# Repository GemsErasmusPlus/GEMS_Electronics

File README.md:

# GEMS_Electronics
GEMS_Electronics repository contains selected results of Erasmus+ project GEMS that are directly related to the electronics design for the GEMS educational hardware.

Project [**GEMS**](https://gems-erasmus.eu/) - Graceful Equalising of Mechatronics Students aims to develop affordable educational hardware for mechatronics students, along with supporting online courses and tutorials. This will allow all students to have equal learning opportunities, regardless of their background or learning needs.

## Disclaimer
Funded by the European Union. Views and opinions expressed are however those of the author(s) only and do not necessarily reflect those of the European Union or CMEPIUS. Neither the European Union nor the granting authority can be held responsible for them.

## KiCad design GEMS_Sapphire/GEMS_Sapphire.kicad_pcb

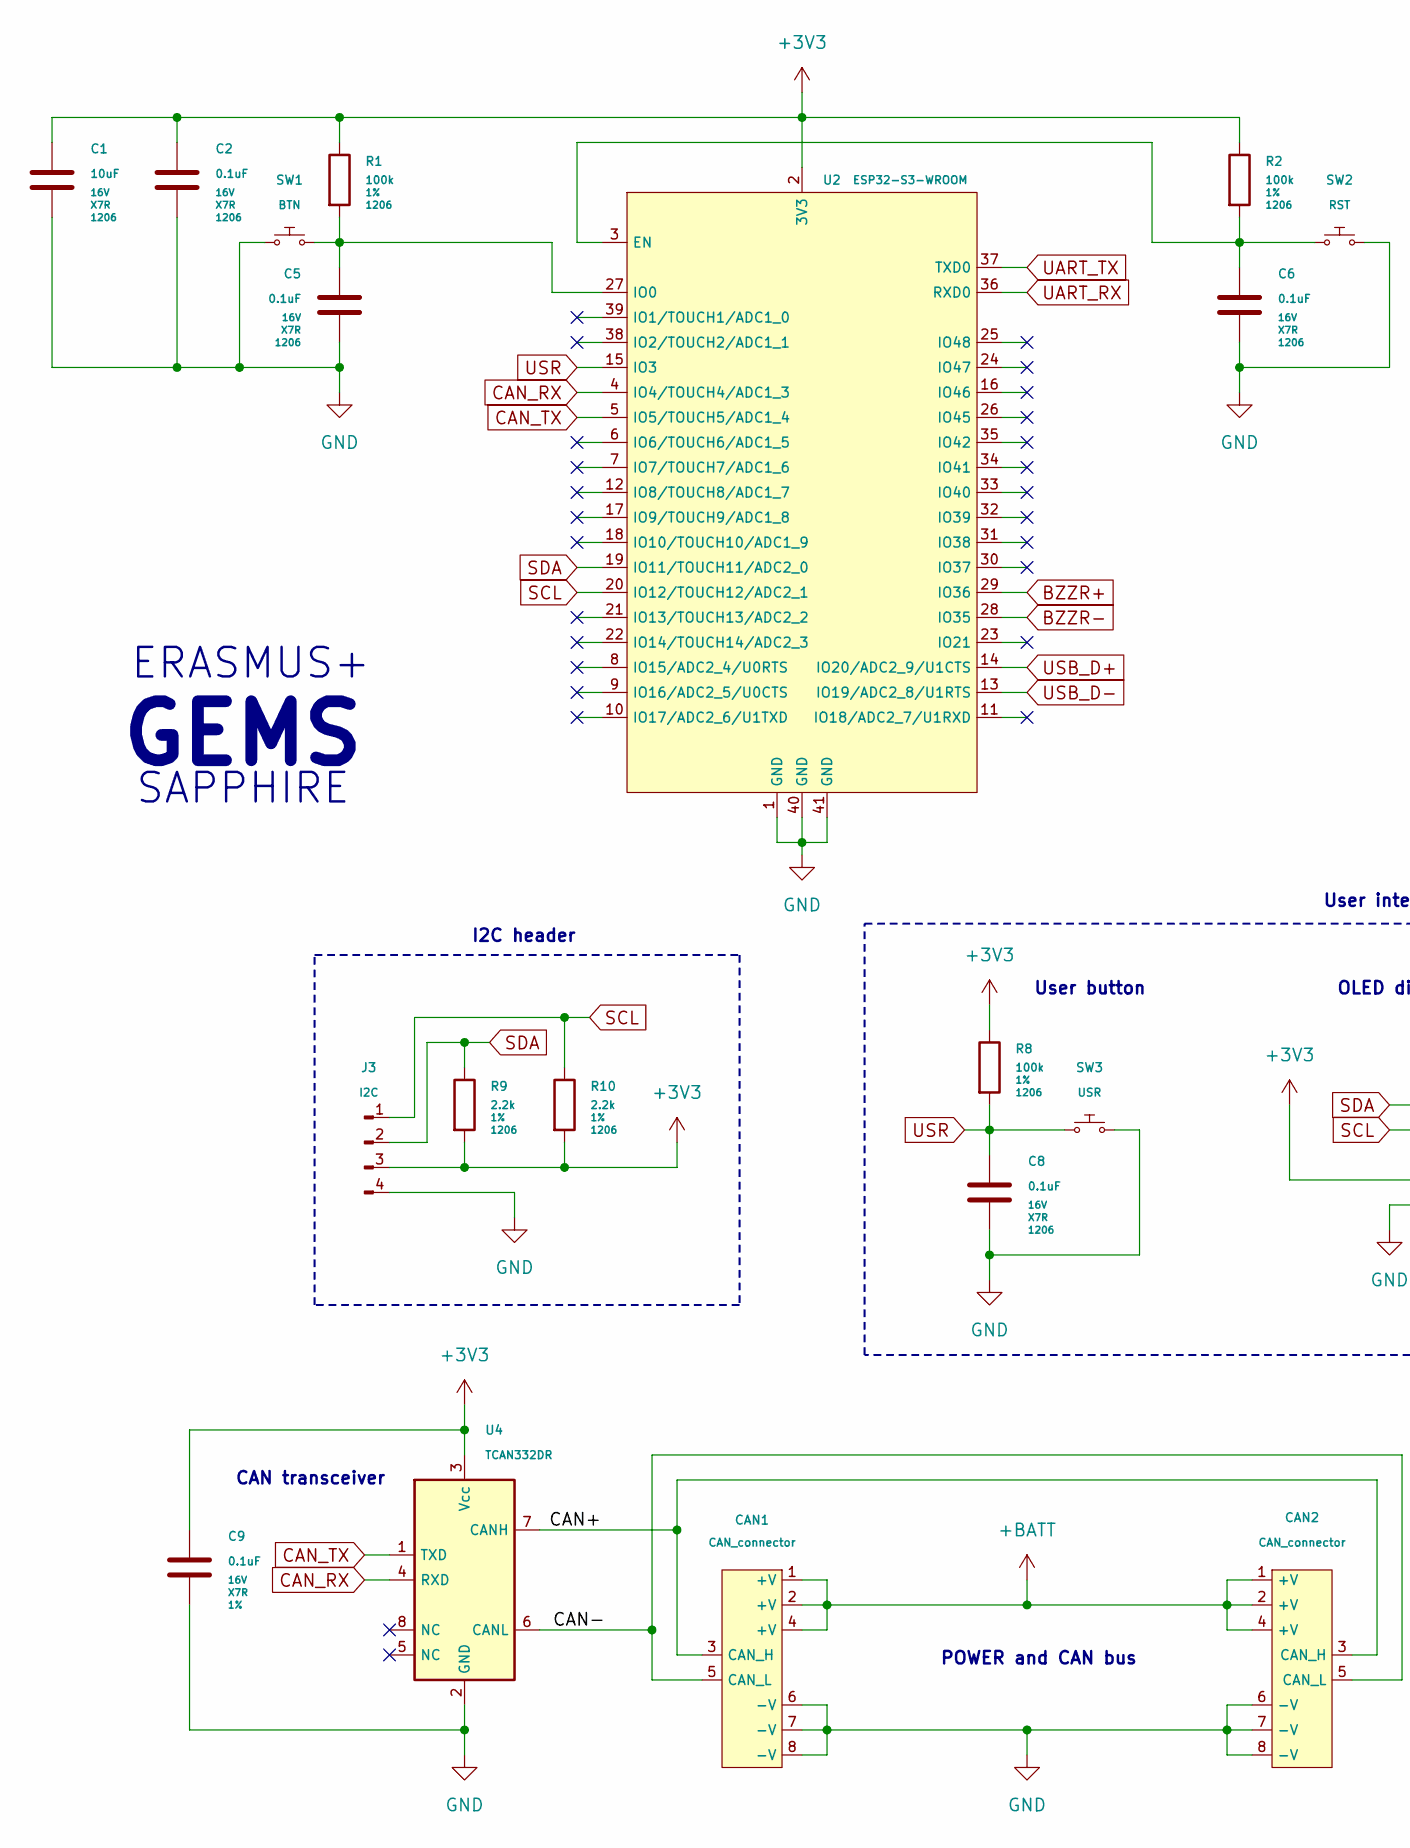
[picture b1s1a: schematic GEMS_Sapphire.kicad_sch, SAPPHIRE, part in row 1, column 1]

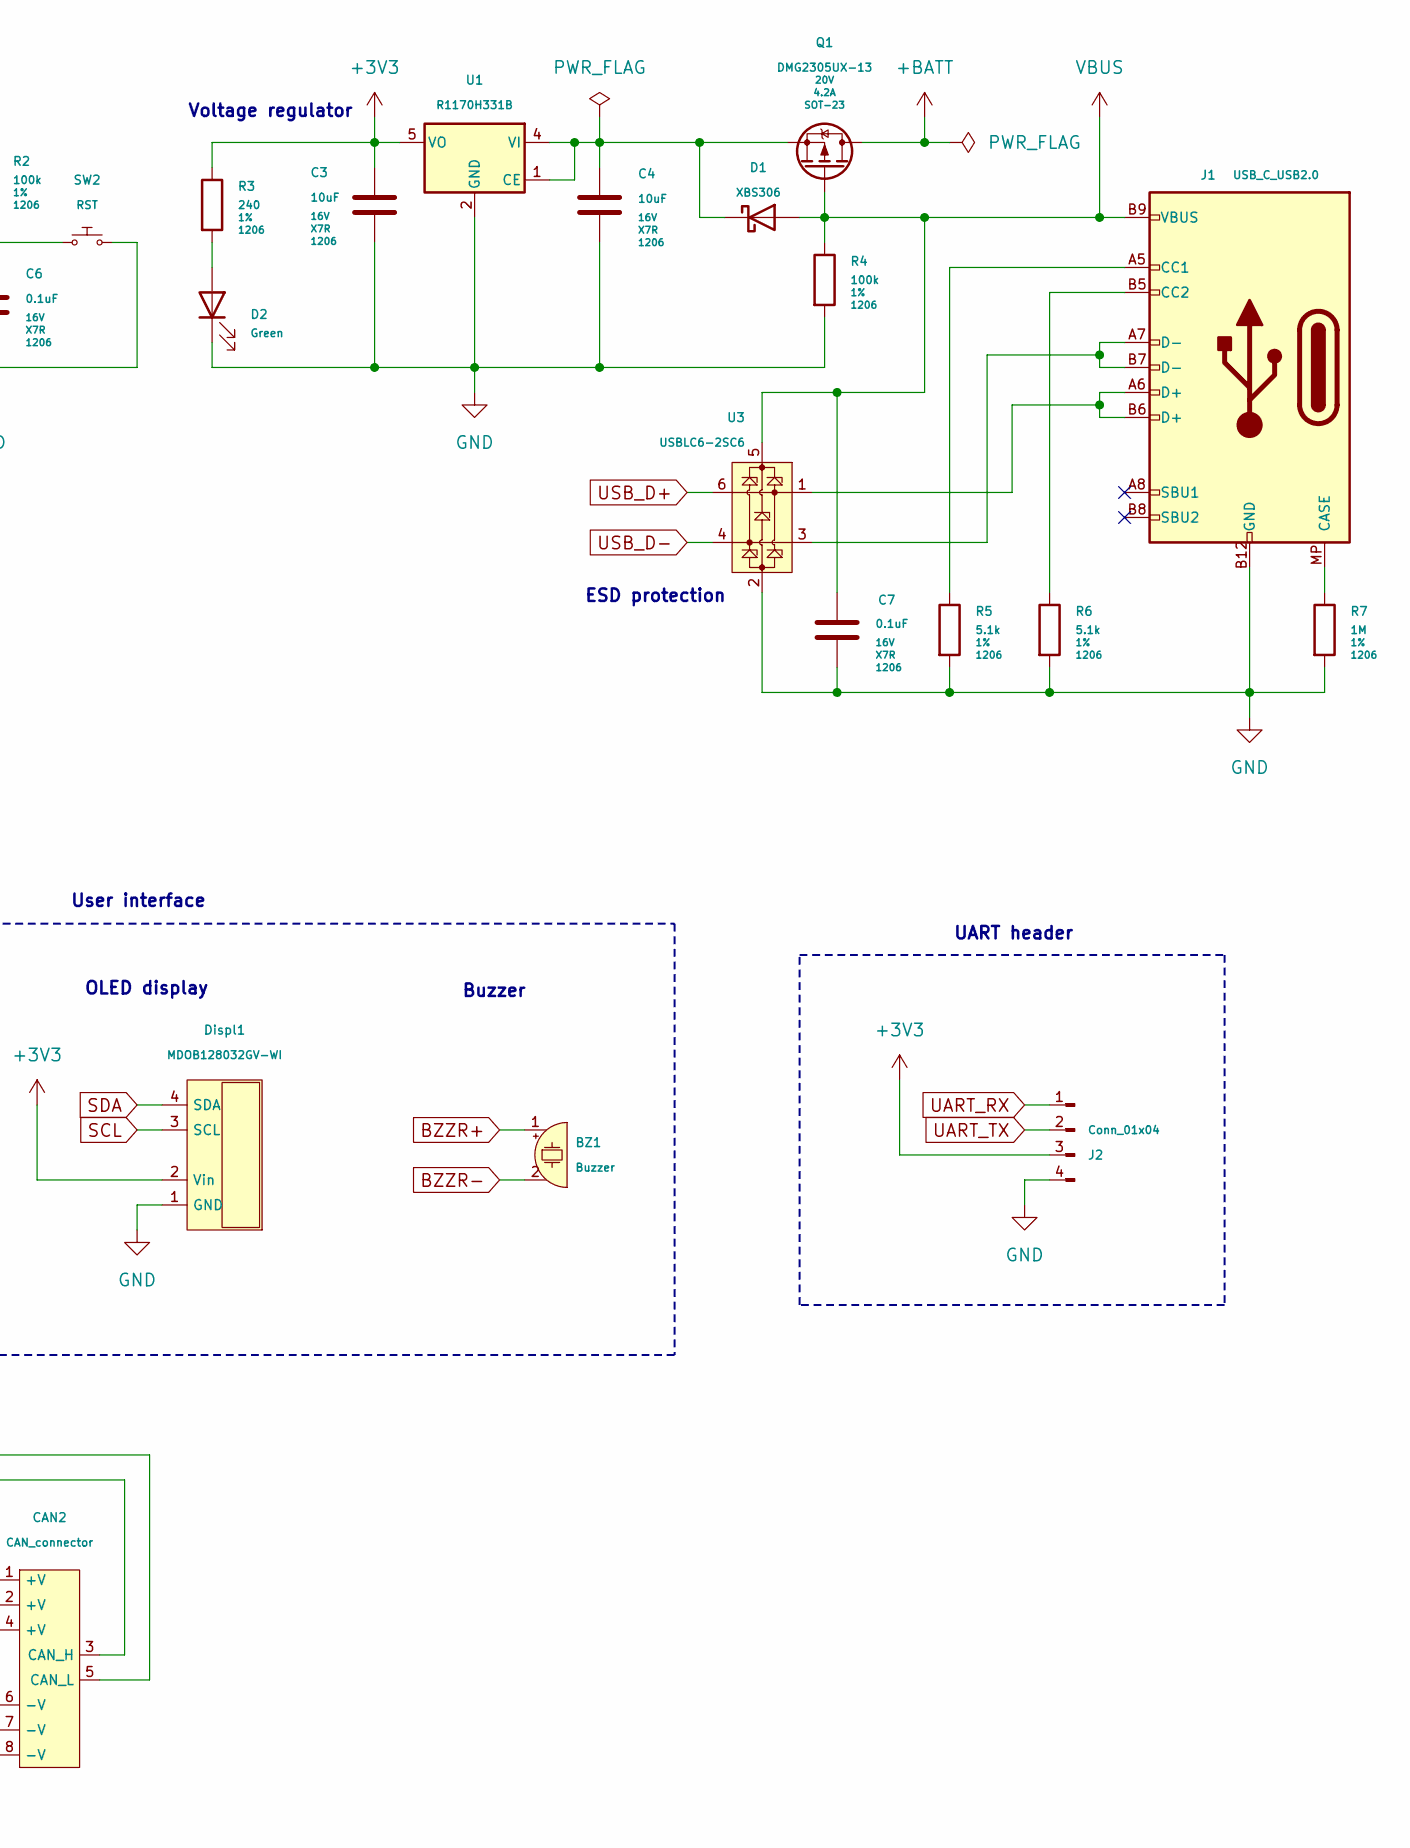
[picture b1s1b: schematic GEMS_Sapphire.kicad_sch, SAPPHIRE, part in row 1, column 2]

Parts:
BZ1: Buzzer; CPT-1117-83-SMT
C1, C3, C4: 10uF; C_1206_(3216); Voltage 16V; Tolerance X7R
C2, C5, C6, C7, C8, C9: 0.1uF; C_1206_(3216); Voltage 16V; Tolerance X7R
CAN1, CAN2: CAN_connector; IDC8_Micro-MaTch
D1: XBS306; DO-214_(SMA); Voltage 60V
D2: Green; LED_D3.0mm
Displ1: MDOB128032GV-WI
J1: USB_C_USB2.0; USB-C_MOLEX-216990-0001
J2: Conn_01x04; PinHeader_1x04_P2.54mm_Vertical
J3: I2C; PinHeader_1x04_P2.54mm_Vertical
Q1: DMG2305UX-13; SOT-23; Voltage 20V
R1, R2, R4, R8: 100k; R_1206_(3216); Tolerance 1%
R3: 240; R_1206_(3216); Tolerance 1%
R5, R6: 5.1k; R_1206_(3216); Tolerance 1%
R7: 1M; R_1206_(3216); Tolerance 1%
R9, R10: 2.2k; R_1206_(3216); Tolerance 1%
SW1: BTN; SW_PUSH_6mm_SMD
SW2: RST; SW_PUSH_6mm_SMD
SW3: USR; SW_PUSH_6mm_SMD
U1: R1170H331B; SOT-89-5
U2: ESP32-S3-WROOM
U3: USBLC6-2SC6; SOT-23-6
U4: TCAN332DR; SOIC-8

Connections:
+3V3: C1.1, C2.1, C3.1, C9.1, Displ1.2 (Vin), J2.3, J3.3, R1.1, R2.1, R3.1, R8.1, R9.2, R10.2, U1.5 (VO), U2.2 (3V3), U4.3 (Vcc)
+BATT: CAN1.1 (+V), CAN1.2 (+V), CAN1.4 (+V), CAN2.1 (+V), CAN2.2 (+V), CAN2.4 (+V), Q1.3 (D)
/CAN+: CAN1.3 (CAN_H), CAN2.3 (CAN_H), U4.7 (CANH)
/CAN-: CAN1.5 (CAN_L), CAN2.5 (CAN_L), U4.6 (CANL)
BZZR+: BZ1.1 (-), U2.29 (IO36)
BZZR-: BZ1.2 (+), U2.28 (IO35)
CAN_RX: U2.4 (IO4/TOUCH4/ADC1_3), U4.4 (RXD)
CAN_TX: U2.5 (IO5/TOUCH5/ADC1_4), U4.1 (TXD)
GND: C1.2, C2.2, C3.2, C4.2, C5.2, C6.2, C7.2, C8.2, C9.2, CAN1.6 (-V), CAN1.7 (-V), CAN1.8 (-V), CAN2.6 (-V), CAN2.7 (-V), CAN2.8 (-V), D2.K, Displ1.1 (GND), J1.A1 (GND), J1.A12 (GND), J1.B1 (GND), J1.B12 (GND), J2.4, J3.4, R4.2, R5.2, R6.2, R7.2, SW1.NO, SW2.COM, SW3.COM, U1.2 (GND), U2.1 (GND), U2.40 (GND), U2.41 (GND), U3.2 (GND), U4.2 (GND)
unnamed: D2.A, R3.2
unnamed: J1.MP (CASE), R7.1
unnamed: J1.A5 (CC1), R5.1
unnamed: J1.B5 (CC2), R6.1
unnamed: J1.A6 (D+), J1.B6 (D+), U3.1 (I/O1)
unnamed: J1.A7 (D-), J1.B7 (D-), U3.3 (I/O2)
unnamed: C4.1, D1.K, Q1.2 (S), U1.1 (CE), U1.4 (VI)
unnamed: C6.1, R2.2, SW2.NO, U2.3 (EN)
unnamed: C5.1, R1.2, SW1.COM, U2.27 (IO0)
SCL: Displ1.3 (SCL), J3.1, R10.1, U2.20 (IO12/TOUCH12/ADC2_1)
SDA: Displ1.4 (SDA), J3.2, R9.1, U2.19 (IO11/TOUCH11/ADC2_0)
UART_RX: J2.1, U2.36 (RXD0)
UART_TX: J2.2, U2.37 (TXD0)
USB_D+: U2.14 (IO20/ADC2_9/U1CTS), U3.6 (I/O1)
USB_D-: U2.13 (IO19/ADC2_8/U1RTS), U3.4 (I/O2)
USR: C8.1, R8.2, SW3.NO, U2.15 (IO3)
VBUS: C7.1, D1.A, J1.A4 (VBUS), J1.A9 (VBUS), J1.B4 (VBUS), J1.B9 (VBUS), Q1.1 (G), R4.1, U3.5 (VBUS)

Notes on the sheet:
ESD protection
Buzzer
OLED display
CAN transceiver
I2C header
ERASMUS+
User button
POWER and CAN bus
SAPPHIRE
GEMS
UART header
Voltage regulator
User interface

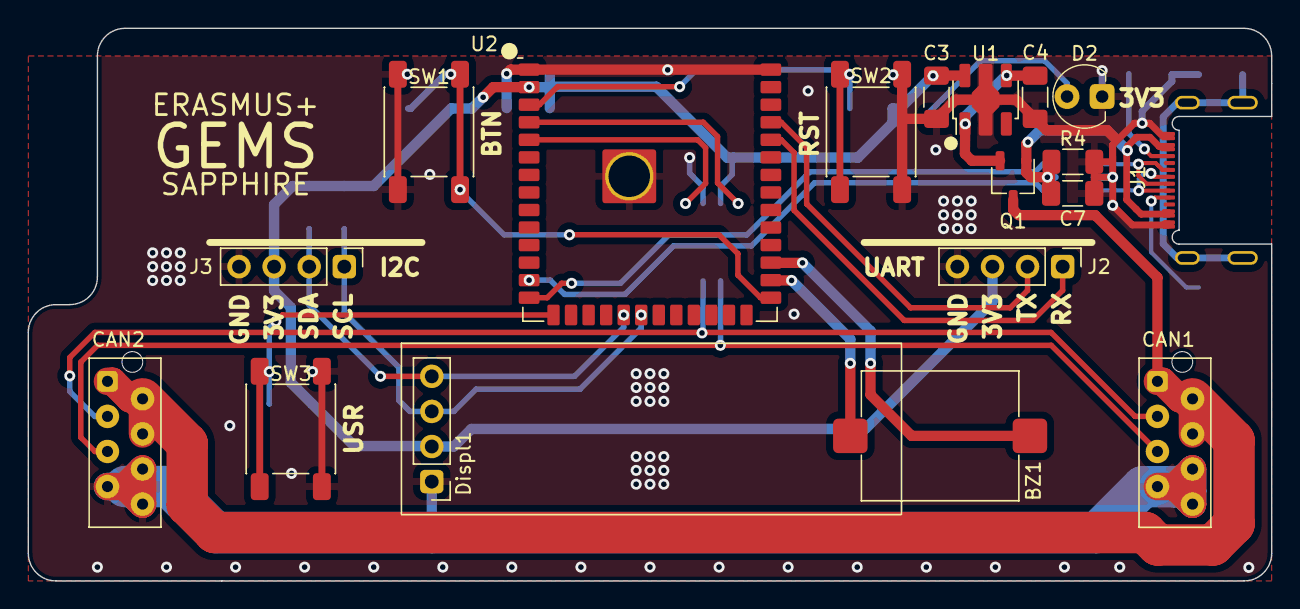
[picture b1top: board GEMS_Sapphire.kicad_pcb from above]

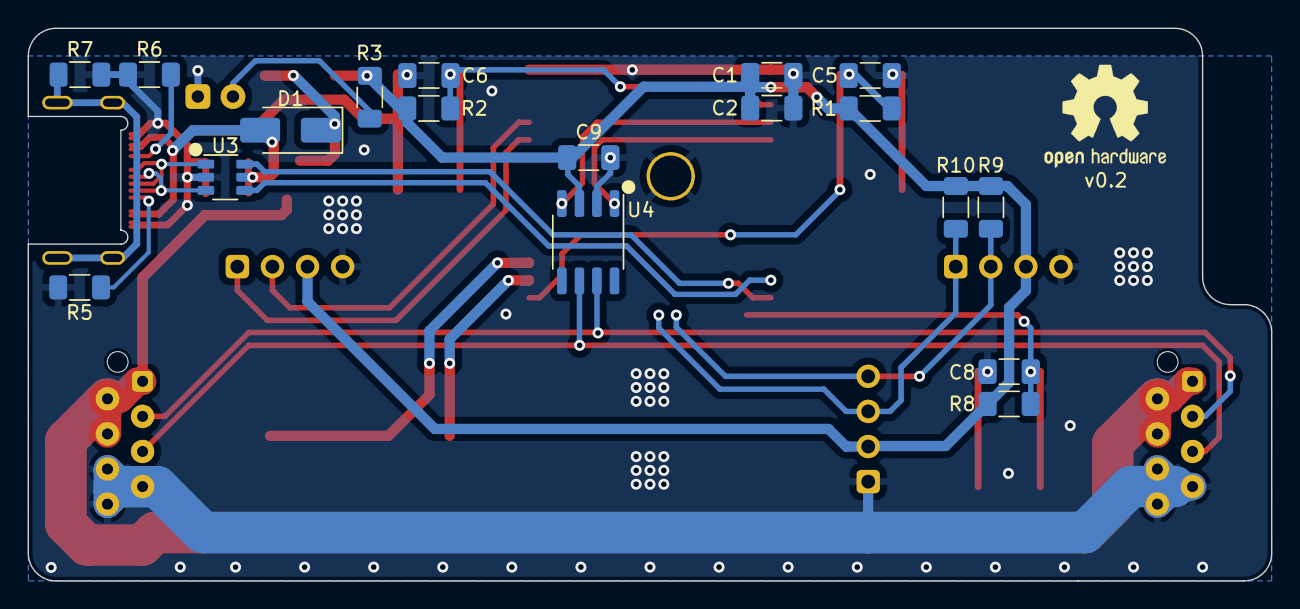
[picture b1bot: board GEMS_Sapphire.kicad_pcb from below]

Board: 2 copper layers, 90.0 x 40.0 mm, 36 parts (18 on the bottom side), 26 nets.

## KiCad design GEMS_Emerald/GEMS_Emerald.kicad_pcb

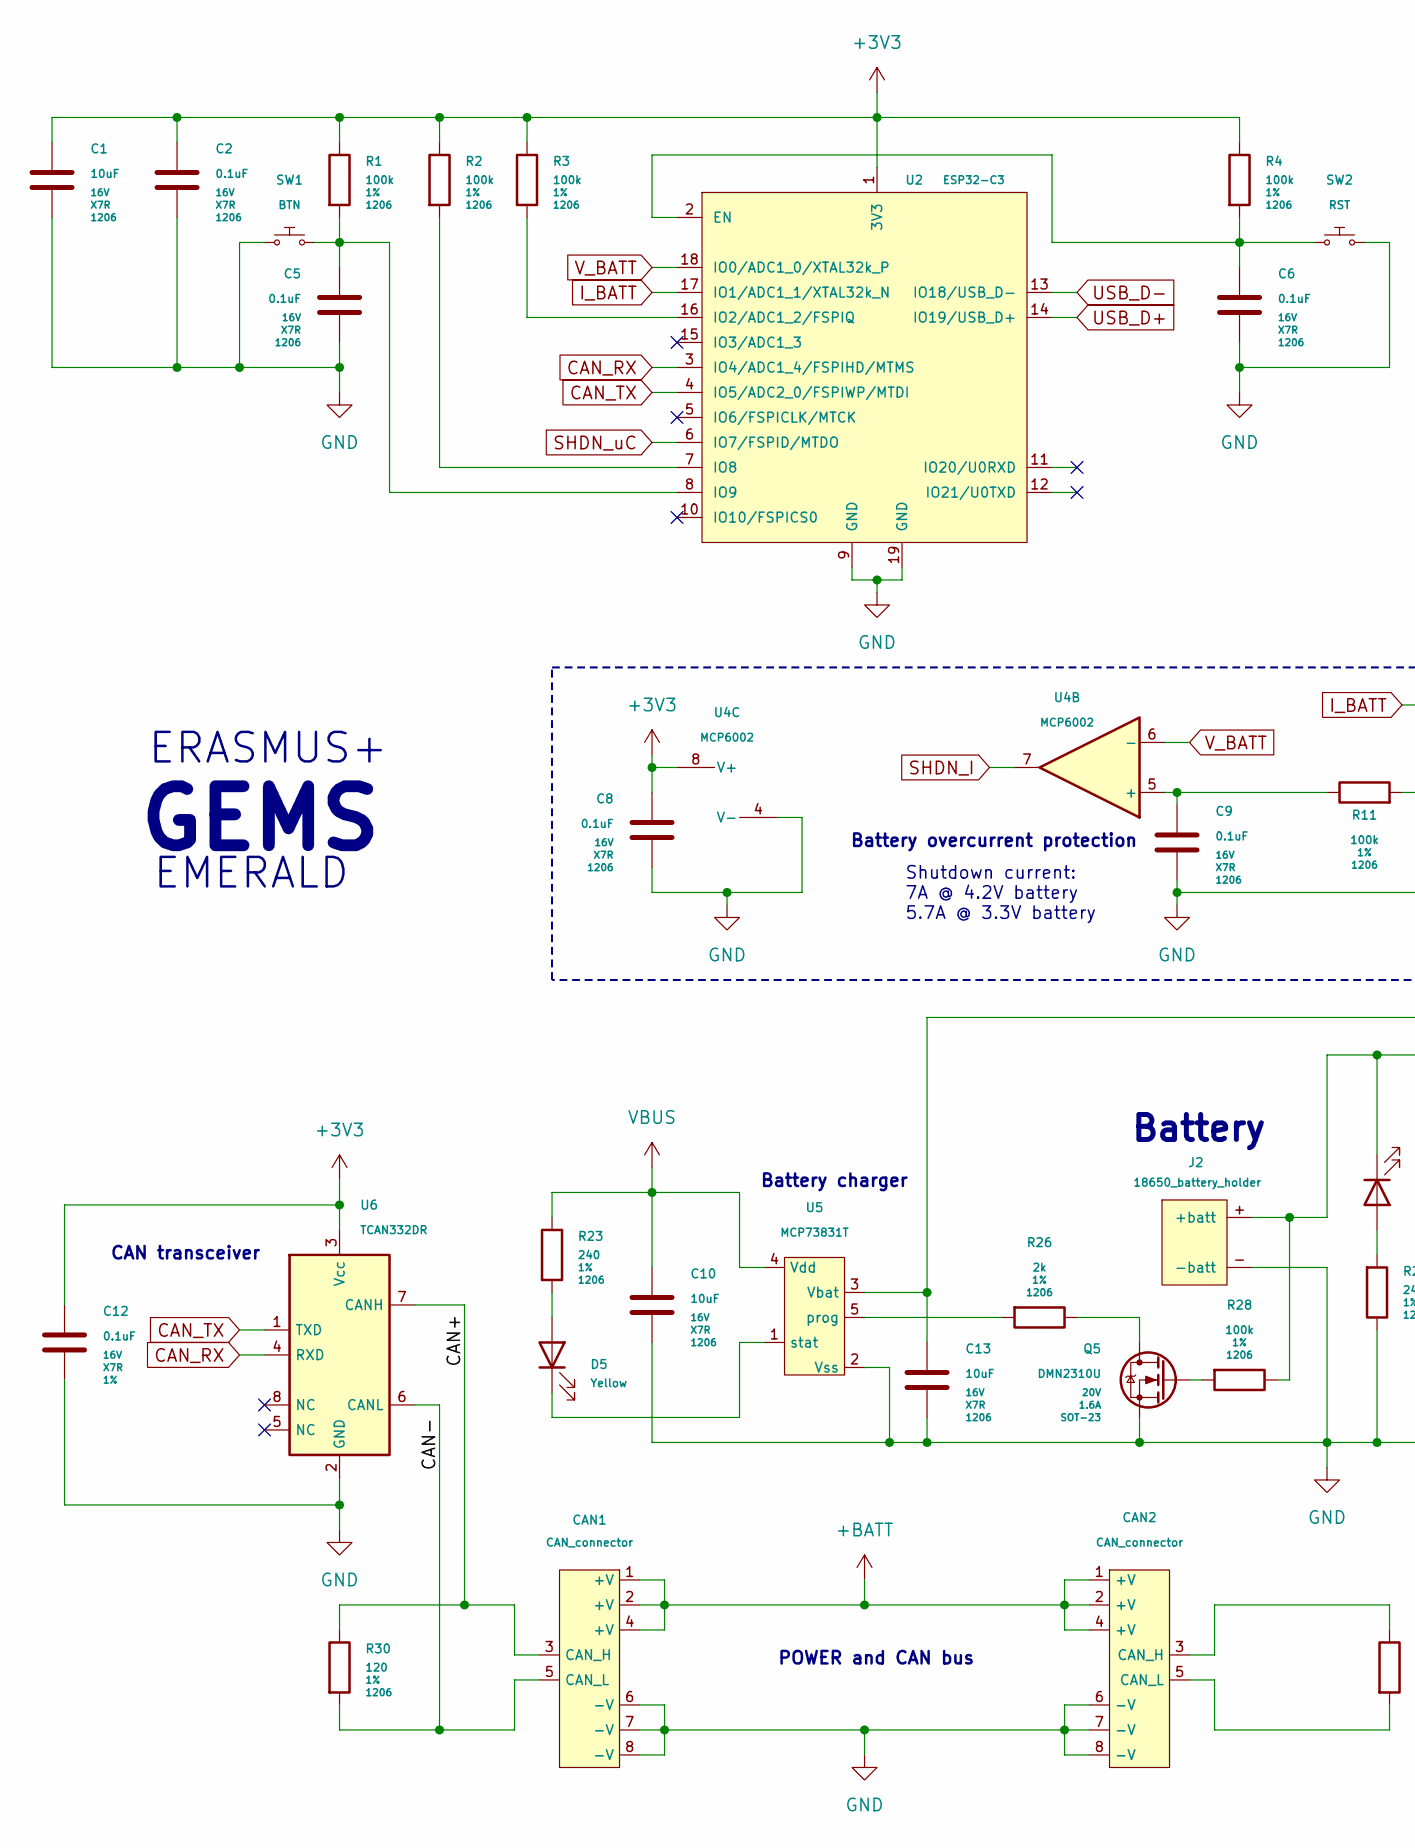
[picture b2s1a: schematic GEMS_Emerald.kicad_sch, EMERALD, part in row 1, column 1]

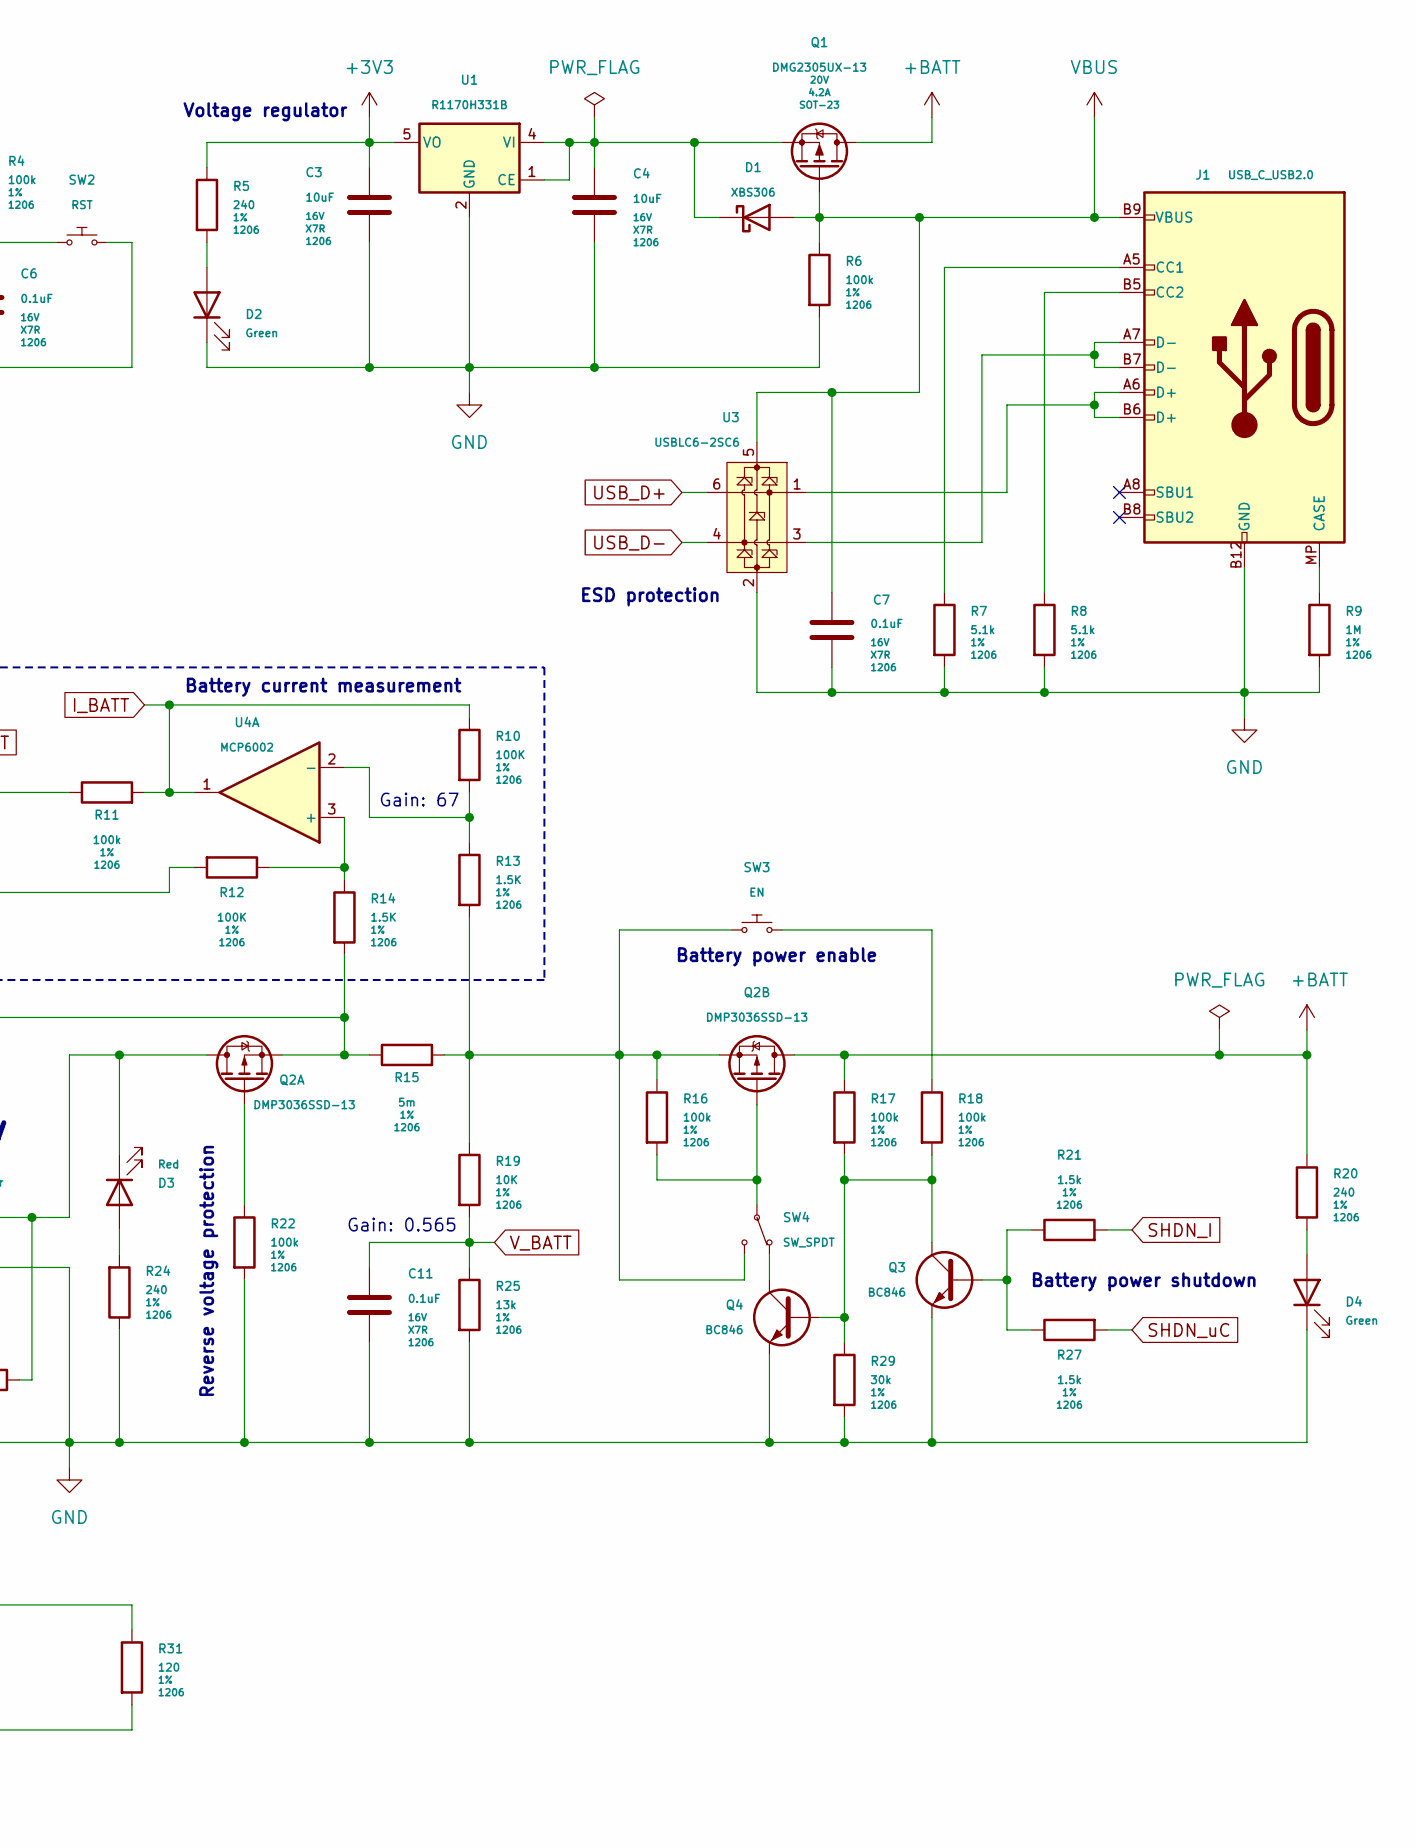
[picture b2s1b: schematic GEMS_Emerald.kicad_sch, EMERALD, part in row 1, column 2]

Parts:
C1, C3, C4, C10, C13: 10uF; C_1206_(3216); Voltage 16V; Tolerance X7R
C2, C5, C6, C7, C8, C9, C11, C12: 0.1uF; C_1206_(3216); Voltage 16V; Tolerance X7R
CAN1, CAN2: CAN_connector; IDC8_Micro-MaTch
D1: XBS306; DO-214_(SMA); Voltage 60V
D2, D4: Green; LED_D3.0mm
D3: Red; LED_D3.0mm
D5: Yellow; LED_D3.0mm
J1: USB_C_USB2.0; USB-C_MOLEX-216990-0001
J2: 18650_battery_holder
Q1: DMG2305UX-13; SOT-23; Voltage 20V
Q2: DMP3036SSD-13; SOIC-8
Q3, Q4: BC846; SOT-23
Q5: DMN2310U; SOT-23; Voltage 20V
R1, R2, R3, R4, R6, R11, R16, R17, R18, R22, R28: 100k; R_1206_(3216); Tolerance 1%
R5, R20, R23, R24: 240; R_1206_(3216); Tolerance 1%
R7, R8: 5.1k; R_1206_(3216); Tolerance 1%
R9: 1M; R_1206_(3216); Tolerance 1%
R10, R12: 100K; R_1206_(3216); Tolerance 1%
R13, R14: 1.5K; R_1206_(3216); Tolerance 1%
R15: 5m; R_1206_(3216); Tolerance 1%
R19: 10K; R_1206_(3216); Tolerance 1%
R21, R27: 1.5k; R_1206_(3216); Tolerance 1%
R25: 13k; R_1206_(3216); Tolerance 1%
R26: 2k; R_1206_(3216); Tolerance 1%
R29: 30k; R_1206_(3216); Tolerance 1%
R30, R31: 120; R_1206_(3216); Tolerance 1%
SW1: BTN; SW_PUSH_6mm_SMD
SW2: RST; SW_PUSH_6mm_SMD
SW3: EN; SW_PUSH_6mm_SMD
SW4: SW_SPDT
U1: R1170H331B; SOT-89-5
U2: ESP32-C3; ESP32-C3-WROOM-02
U3: USBLC6-2SC6; SOT-23-6
U4: MCP6002; SOIC-8
U5: MCP73831T; SOT-23-5
U6: TCAN332DR; SOIC-8

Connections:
+3V3: C1.1, C2.1, C3.1, C8.1, C12.1, R1.1, R2.1, R3.1, R4.1, R5.1, U1.5 (VO), U2.1 (3V3), U4.8 (V+), U6.3 (Vcc)
+BATT: CAN1.1 (+V), CAN1.2 (+V), CAN1.4 (+V), CAN2.1 (+V), CAN2.2 (+V), CAN2.4 (+V), Q1.3 (D), Q2.5 (D2), Q2.6 (D2), R17.1, R20.1
/CAN+: CAN1.3 (CAN_H), R30.1, U6.7 (CANH)
/CAN-: CAN1.5 (CAN_L), R30.2, U6.6 (CANL)
CAN_RX: U2.3 (IO4/ADC1_4/FSPIHD/MTMS), U6.4 (RXD)
CAN_TX: U2.4 (IO5/ADC2_0/FSPIWP/MTDI), U6.1 (TXD)
GND: C1.2, C2.2, C3.2, C4.2, C5.2, C6.2, C7.2, C8.2, C9.2, C10.2, C11.2, C12.2, C13.2, CAN1.6 (-V), CAN1.7 (-V), CAN1.8 (-V), CAN2.6 (-V), CAN2.7 (-V), CAN2.8 (-V), D2.K, D4.K, J1.A1 (GND), J1.A12 (GND), J1.B1 (GND), J1.B12 (GND), J2.- (-batt), Q3.2 (E), Q4.2 (E), Q5.2 (S), R6.2, R7.2, R8.2, R9.2, R12.2, R22.2, R24.1, R25.2, R29.2, SW1.NO, SW2.COM, U1.2 (GND), U2.9 (GND), U2.19 (GND), U3.2 (GND), U4.4 (V-), U5.2 (Vss), U6.2 (GND)
I_BATT: R10.1, R11.2, U2.17 (IO1/ADC1_1/XTAL32k_N), U4.1
unnamed: CAN2.3 (CAN_H), R31.1
unnamed: CAN2.5 (CAN_L), R31.2
unnamed: D2.A, R5.2
unnamed: D3.A, R24.2
unnamed: D4.A, R20.2
unnamed: D5.A, R23.2
unnamed: J1.MP (CASE), R9.1
unnamed: J1.A5 (CC1), R7.1
unnamed: J1.B5 (CC2), R8.1
unnamed: J1.A6 (D+), J1.B6 (D+), U3.1 (I/O1)
unnamed: J1.A7 (D-), J1.B7 (D-), U3.3 (I/O2)
unnamed: D3.K, J2.+ (+batt), Q2.7 (D1), Q2.8 (D1), R28.1
unnamed: C4.1, D1.K, Q1.2 (S), U1.1 (CE), U1.4 (VI)
unnamed: Q2.2 (G1), R22.1
unnamed: C13.1, Q2.1 (S1), R14.2, R15.1, U5.3 (Vbat)
unnamed: Q2.4 (G2), R16.2, SW4.COM
unnamed: Q2.3 (S2), R13.2, R15.2, R16.1, R19.1, SW3.NO, SW4.RC
unnamed: Q3.1 (B), R21.1, R27.1
unnamed: Q3.3 (C), Q4.1 (B), R17.2, R18.2, R29.1
unnamed: Q4.3 (C), SW4.LC
unnamed: Q5.3 (D), R26.1
unnamed: Q5.1 (G), R28.2
unnamed: R18.1, SW3.COM
unnamed: C6.1, R4.2, SW2.NO, U2.2 (EN)
unnamed: R3.2, U2.16 (IO2/ADC1_2/FSPIQ)
unnamed: R2.2, U2.7 (IO8)
unnamed: C5.1, R1.2, SW1.COM, U2.8 (IO9)
unnamed: R12.1, R14.1, U4.3 (+)
unnamed: R10.2, R13.1, U4.2 (-)
unnamed: C9.1, R11.1, U4.5 (+)
unnamed: R26.2, U5.5 (prog)
unnamed: D5.K, U5.1 (stat)
SHDN_I: R21.2, U4.7
SHDN_uC: R27.2, U2.6 (IO7/FSPID/MTDO)
USB_D+: U2.14 (IO19/USB_D+), U3.6 (I/O1)
USB_D-: U2.13 (IO18/USB_D-), U3.4 (I/O2)
VBUS: C7.1, C10.1, D1.A, J1.A4 (VBUS), J1.A9 (VBUS), J1.B4 (VBUS), J1.B9 (VBUS), Q1.1 (G), R6.1, R23.1, U3.5 (VBUS), U5.4 (Vdd)
V_BATT: C11.1, R19.2, R25.1, U2.18 (IO0/ADC1_0/XTAL32k_P), U4.6 (-)

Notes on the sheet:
Battery
Battery charger
ESD protection
Gain: 67
CAN transceiver
ERASMUS+
Reverse voltage protection
POWER and CAN bus
EMERALD
GEMS
Voltage regulator
Shutdown current: 7A @ 4.2V battery 5.7A @ 3.3V battery
Battery overcurrent protection
Battery power enable
Battery power shutdown
Gain: 0.565
Battery current measurement

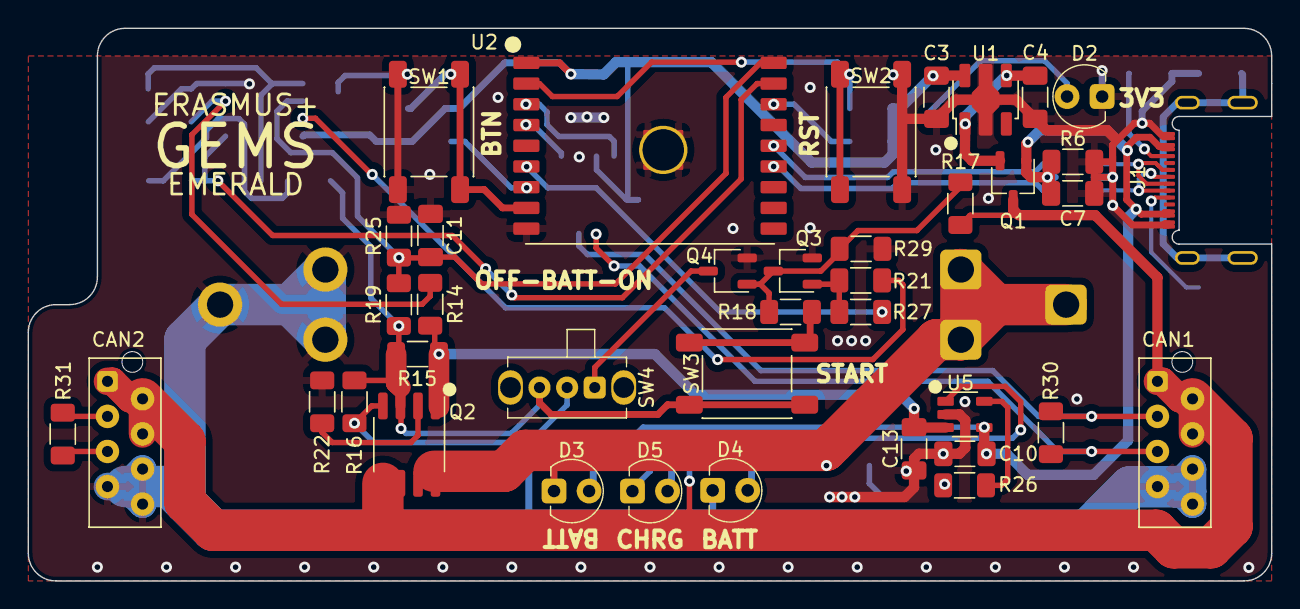
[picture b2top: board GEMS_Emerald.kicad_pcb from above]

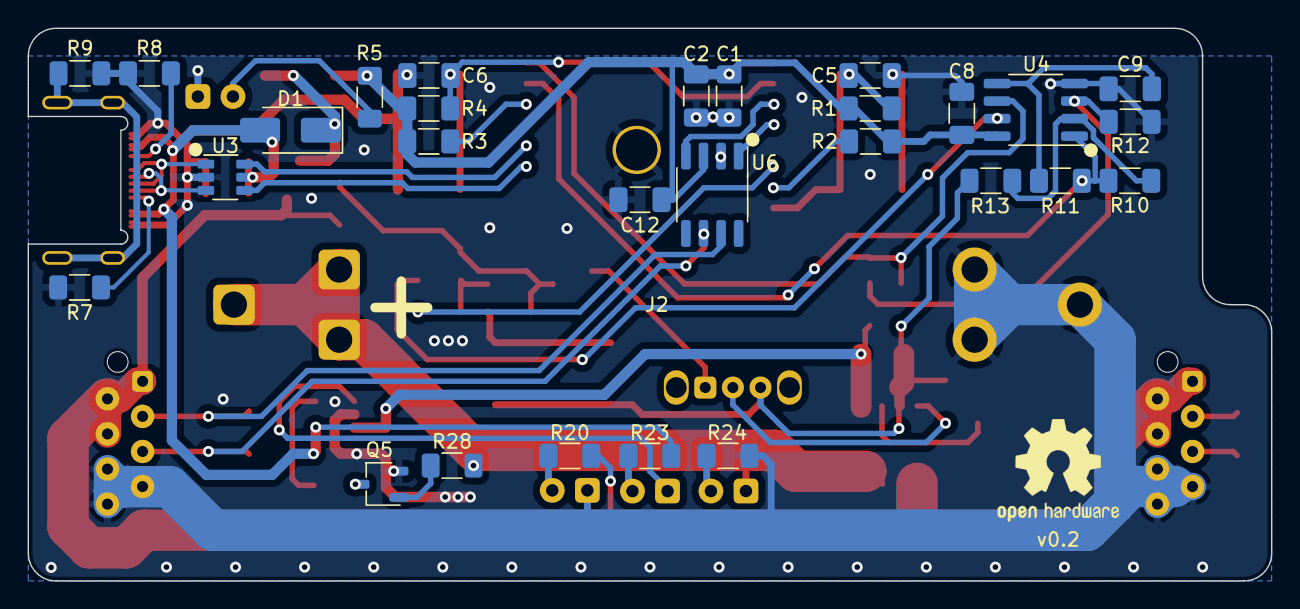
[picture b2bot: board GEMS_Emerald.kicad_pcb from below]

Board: 2 copper layers, 90.0 x 40.0 mm, 68 parts (29 on the bottom side), 46 nets.
